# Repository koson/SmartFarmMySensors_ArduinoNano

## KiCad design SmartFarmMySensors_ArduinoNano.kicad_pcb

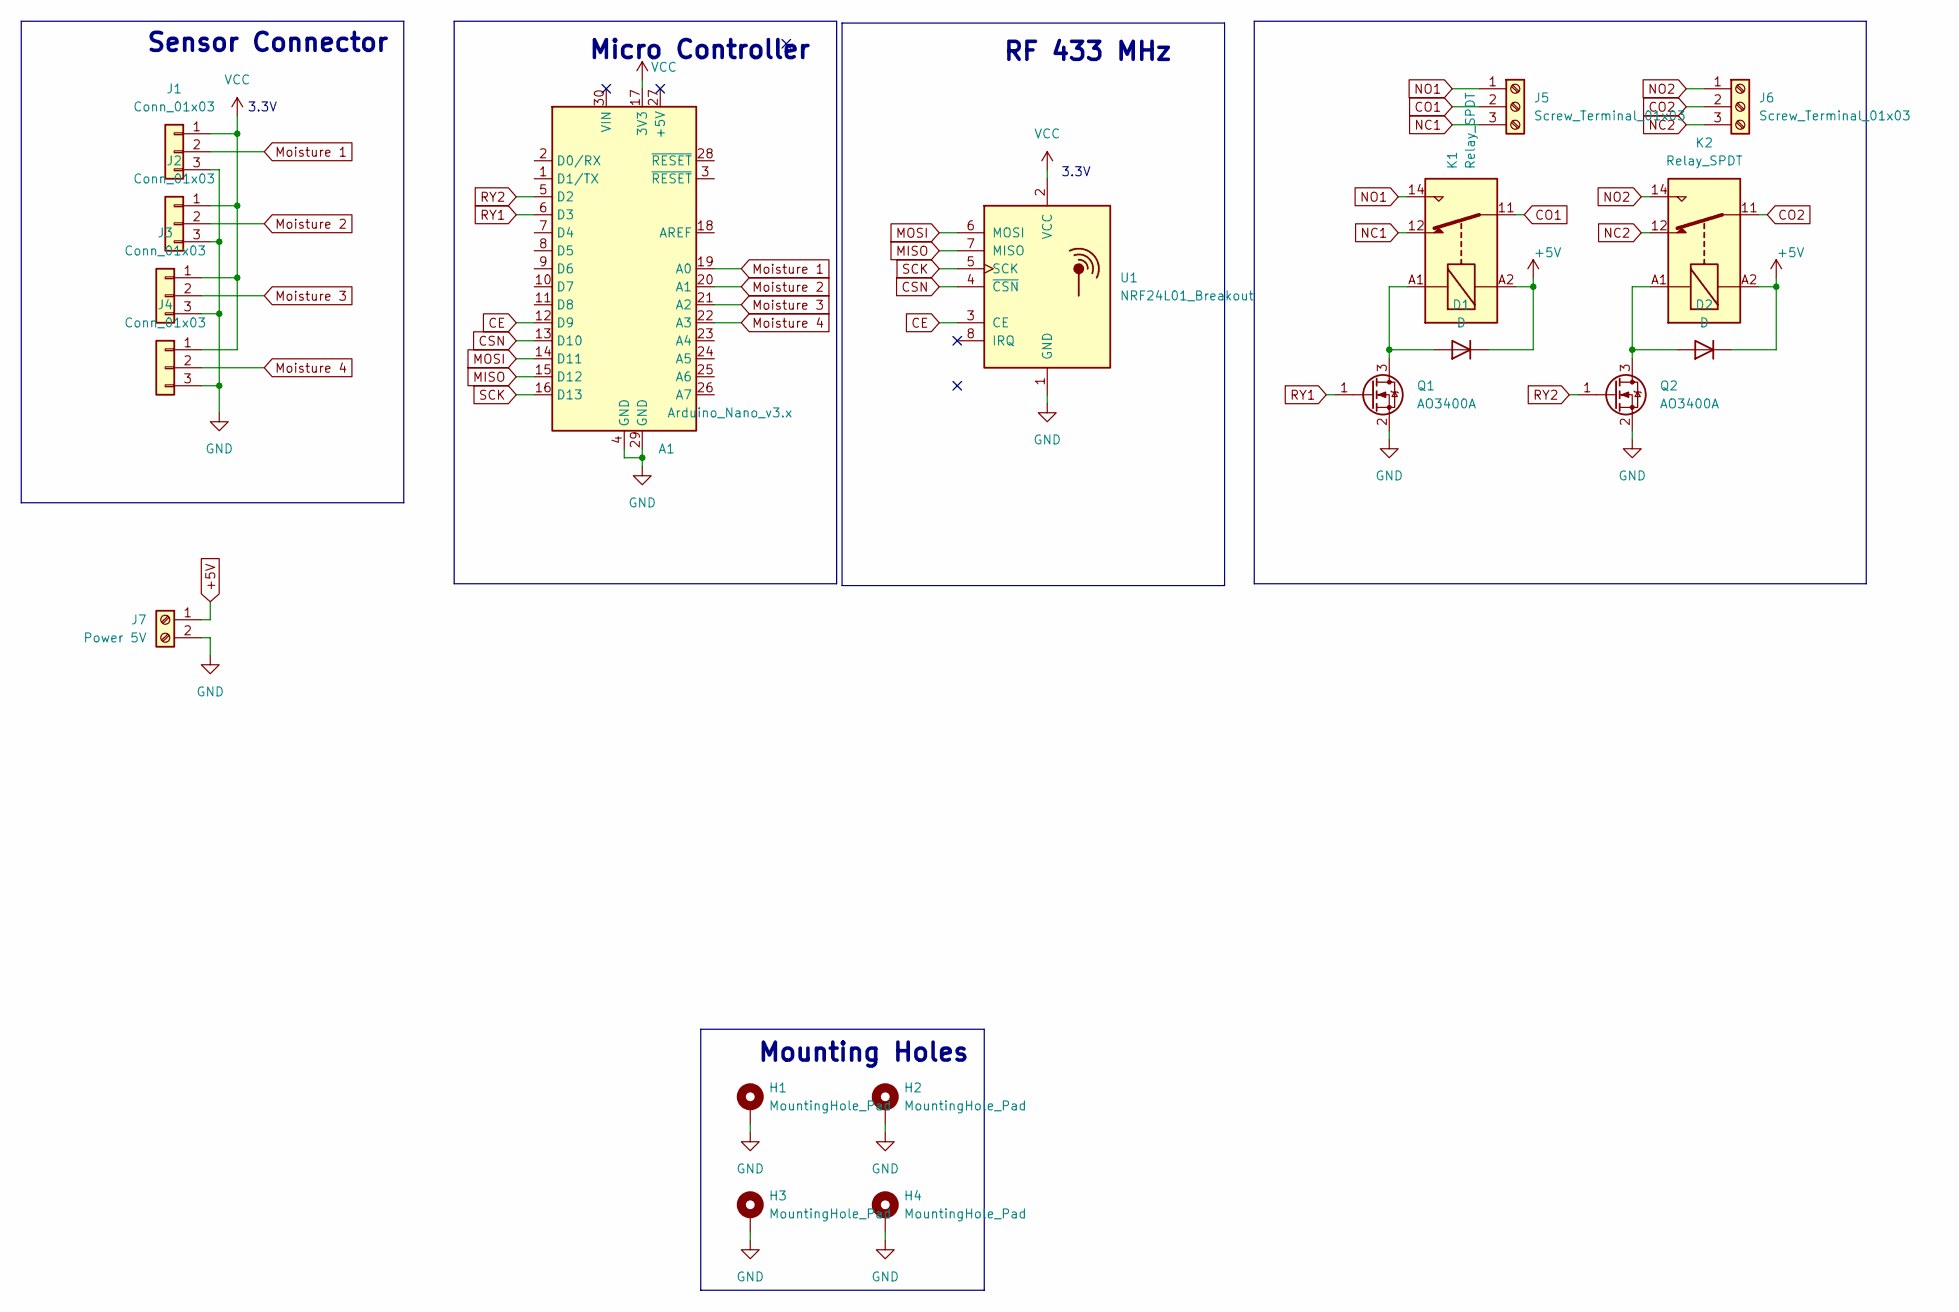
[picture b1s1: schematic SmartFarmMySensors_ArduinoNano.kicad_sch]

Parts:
A1: Arduino_Nano_v3.x; Arduino_Nano
D1, D2: D; D_SMA
H1, H2, H3, H4: MountingHole_Pad; MountingHole_3.2mm_M3_Pad_Via
J1, J2, J3, J4: Conn_01x03; JST_PH_B3B-PH-K_1x03_P2.00mm_Vertical
J5, J6: Screw_Terminal_01x03; TerminalBlock_Xinya_XY308-2.54-3P_1x03_P2.54mm_Horizontal
J7: Power 5V; TerminalBlock_Xinya_XY308-2.54-2P_1x02_P2.54mm_Horizontal
K1, K2: Relay_SPDT; Relay_SPDT_Finder_36.11
Q1, Q2: AO3400A; SOT-23
U1: NRF24L01_Breakout; nRF24L01_Breakout

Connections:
+5V: D1.1 (K), D2.1 (K), J7.1, K1.A2, K2.A2
CE: A1.12 (D9), U1.3 (CE)
CO1: J5.2, K1.11
CO2: J6.2, K2.11
CSN: A1.13 (D10), U1.4 (~CSN)
GND: A1.4 (GND), A1.29 (GND), H1.1, H2.1, H3.1, H4.1, J1.3, J2.3, J3.3, J4.3, J7.2, Q1.2 (S), Q2.2 (S), U1.1 (GND)
MISO: A1.15 (D12), U1.7 (MISO)
MOSI: A1.14 (D11), U1.6 (MOSI)
Moisture 1: A1.19 (A0), J1.2
Moisture 2: A1.20 (A1), J2.2
Moisture 3: A1.21 (A2), J3.2
Moisture 4: A1.22 (A3), J4.2
NC1: J5.3, K1.12
NC2: J6.3, K2.12
NO1: J5.1, K1.14
NO2: J6.1, K2.14
unnamed: D1.2 (A), K1.A1, Q1.3 (D)
unnamed: D2.2 (A), K2.A1, Q2.3 (D)
RY1: A1.6 (D3), Q1.1 (G)
RY2: A1.5 (D2), Q2.1 (G)
SCK: A1.16 (D13), U1.5 (SCK)
VCC: A1.17 (3V3), J1.1, J2.1, J3.1, J4.1, U1.2 (VCC)

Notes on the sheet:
Sensor Connector
RF 433 MHz
Mounting Holes
Micro Controller
3.3V

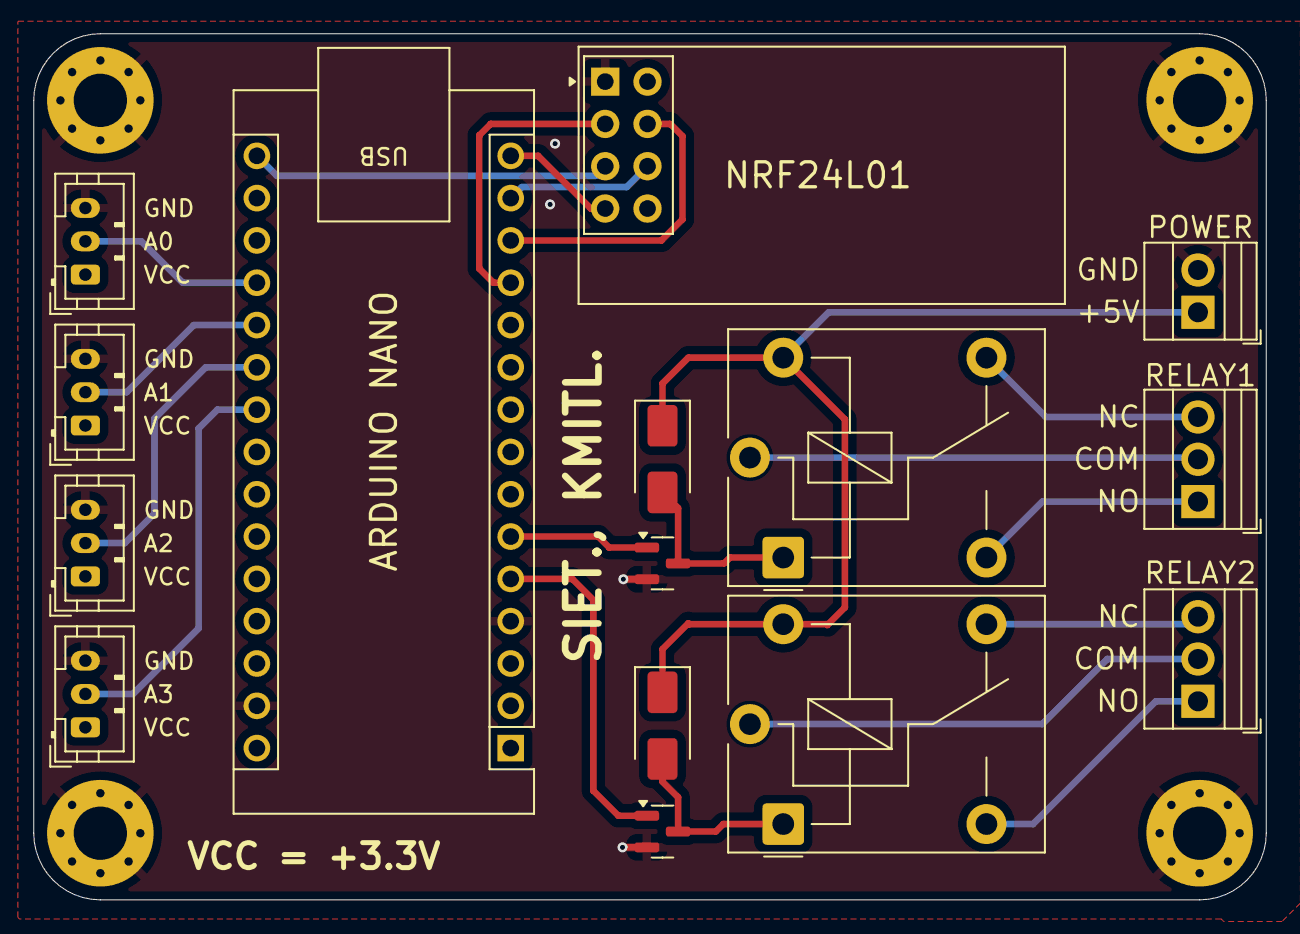
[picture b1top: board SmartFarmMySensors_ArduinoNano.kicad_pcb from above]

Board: 4 copper layers, 74.0 x 52.0 mm, 19 parts (0 on the bottom side), 22 nets.

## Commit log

2025-02-11 ready to order
2025-03-29 Implement initial project structure
